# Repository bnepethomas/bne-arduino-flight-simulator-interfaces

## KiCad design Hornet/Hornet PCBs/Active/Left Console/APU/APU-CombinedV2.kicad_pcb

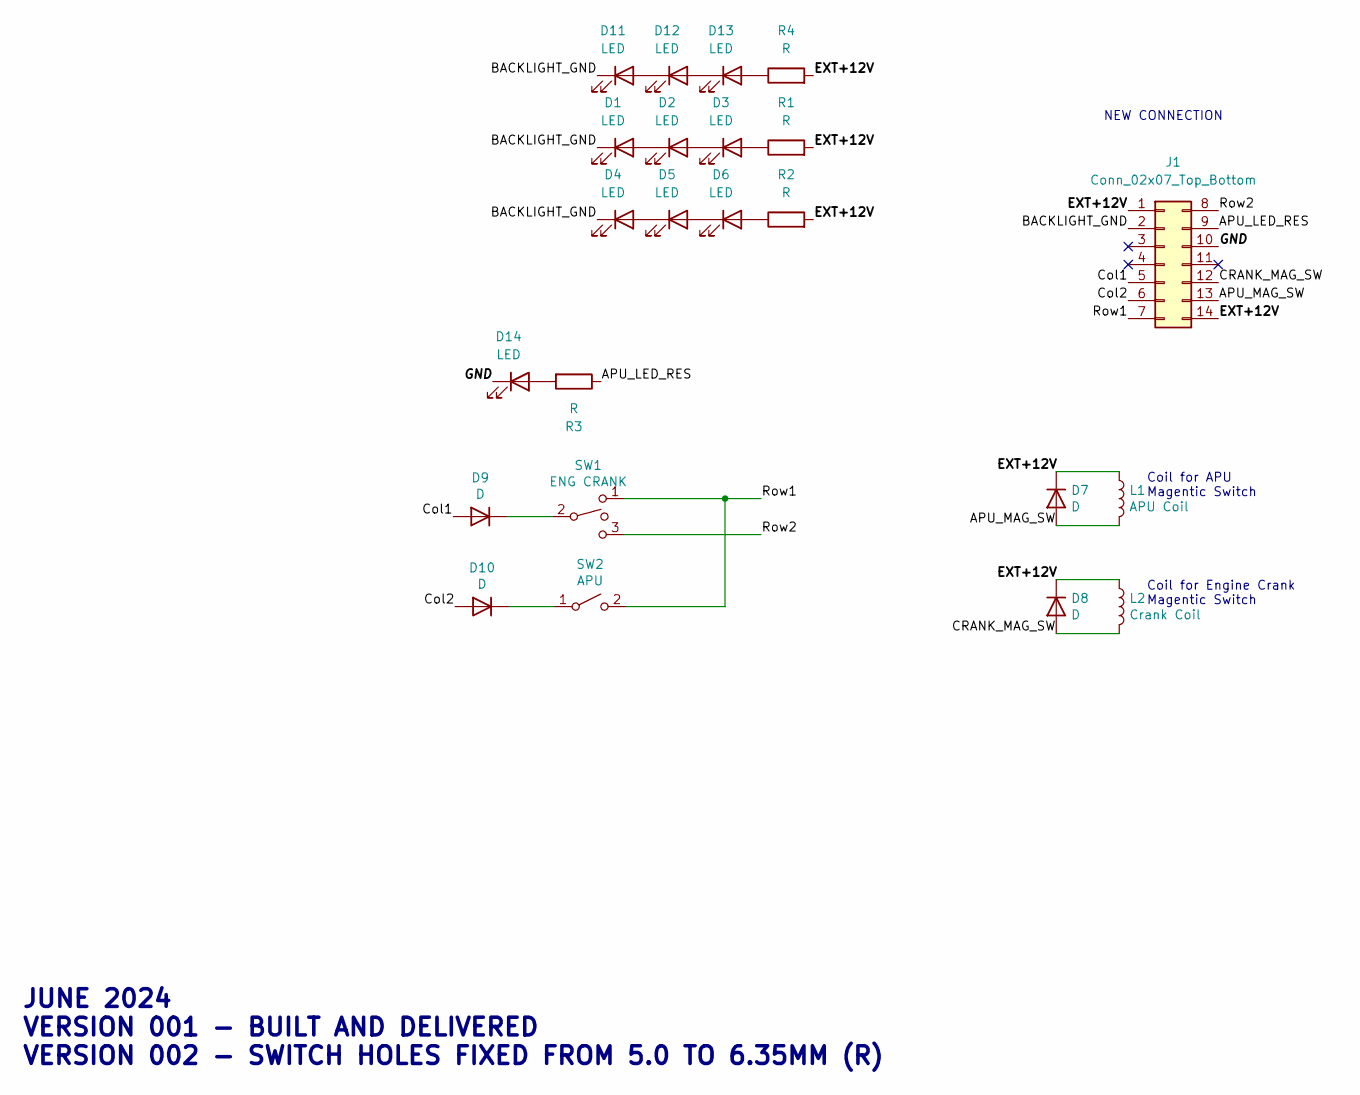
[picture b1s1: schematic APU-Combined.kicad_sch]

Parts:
D1, D2, D3, D4, D5, D6, D11, D12, D13, D14: LED; LED_D3.0mm_FlatTop
D7, D8: D; D_DO-41_SOD81_P7.62mm_Horizontal
D9, D10: D; D_A-405_P7.62mm_Horizontal-SIGNAL
J1: Conn_02x07_Top_Bottom; IDC-Header_2x07_P2.54mm_Vertical
L1: APU Coil; JST_XH_B2B-XH-A_1x02_P2.50mm_Vertical
L2: Crank Coil; JST_XH_B2B-XH-A_1x02_P2.50mm_Vertical
R1, R2, R3, R4: R; R_Axial_DIN0204_L3.6mm_D1.6mm_P7.62mm_Horizontal
SW1: ENG CRANK; JST_XH_B3B-XH-A_1x03_P2.50mm_Vertical
SW2: APU; JST_XH_B2B-XH-A_1x02_P2.50mm_Vertical

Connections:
/APU_LED_RES: J1.9, R3.1
/APU_MAG_SW: D7.2 (A), J1.13, L1.2
/BACKLIGHT_GND: D1.1 (K), D4.1 (K), D11.1 (K), J1.2
/CRANK_MAG_SW: D8.2 (A), J1.12, L2.2
/Col1: D9.2 (A), J1.5
/Col2: D10.2 (A), J1.6
/EXT+12V: D7.1 (K), D8.1 (K), J1.1, J1.14, L1.1, L2.1, R1.2, R2.2, R4.2
/GND: D14.1 (K), J1.10
/Row1: J1.7, SW1.1, SW2.2 (B)
/Row2: J1.8, SW1.3
unnamed: D1.2 (A), D2.1 (K)
unnamed: D2.2 (A), D3.1 (K)
unnamed: D3.2 (A), R1.1
unnamed: D4.2 (A), D5.1 (K)
unnamed: D5.2 (A), D6.1 (K)
unnamed: D6.2 (A), R2.1
unnamed: D9.1 (K), SW1.2
unnamed: D10.1 (K), SW2.1 (A)
unnamed: D11.2 (A), D12.1 (K)
unnamed: D12.2 (A), D13.1 (K)
unnamed: D13.2 (A), R4.1
unnamed: D14.2 (A), R3.2

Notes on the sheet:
NEW CONNECTION
Coil for Engine Crank Magentic Switch
JUNE 2024 VERSION 001 - BUILT AND DELIVERED VERSION 002 - SWITCH HOLES FIXED FROM 5.0 TO 6.35MM (R)
Coil for APU Magentic Switch

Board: 2 copper layers, 23 parts (13 on the bottom side), 22 nets, no tracks yet.

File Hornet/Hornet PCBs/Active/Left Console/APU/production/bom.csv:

Designator,Footprint,Quantity,Value,LCSC Part #
"D1, D11, D12, D13, D14, D2, D3, D4, D5, D6",LED_D3.0mm_FlatTop,10,LED,
"D10, D9",D_A-405_P7.62mm_Horizontal-SIGNAL,2,D,
"D7, D8",D_DO-41_SOD81_P7.62mm_Horizontal,2,D,
J1,IDC-Header_2x07_P2.54mm_Vertical,1,Conn_02x07_Top_Bottom,
L1,JST_XH_B2B-XH-A_1x02_P2.50mm_Vertical,1,APU Coil,
L2,JST_XH_B2B-XH-A_1x02_P2.50mm_Vertical,1,Crank Coil,
"R1, R2, R3, R4",R_Axial_DIN0204_L3.6mm_D1.6mm_P7.62mm_Horizontal,4,R,
SW1,JST_XH_B3B-XH-A_1x03_P2.50mm_Vertical,1,ENG CRANK,
SW2,JST_XH_B2B-XH-A_1x02_P2.50mm_Vertical,1,APU,

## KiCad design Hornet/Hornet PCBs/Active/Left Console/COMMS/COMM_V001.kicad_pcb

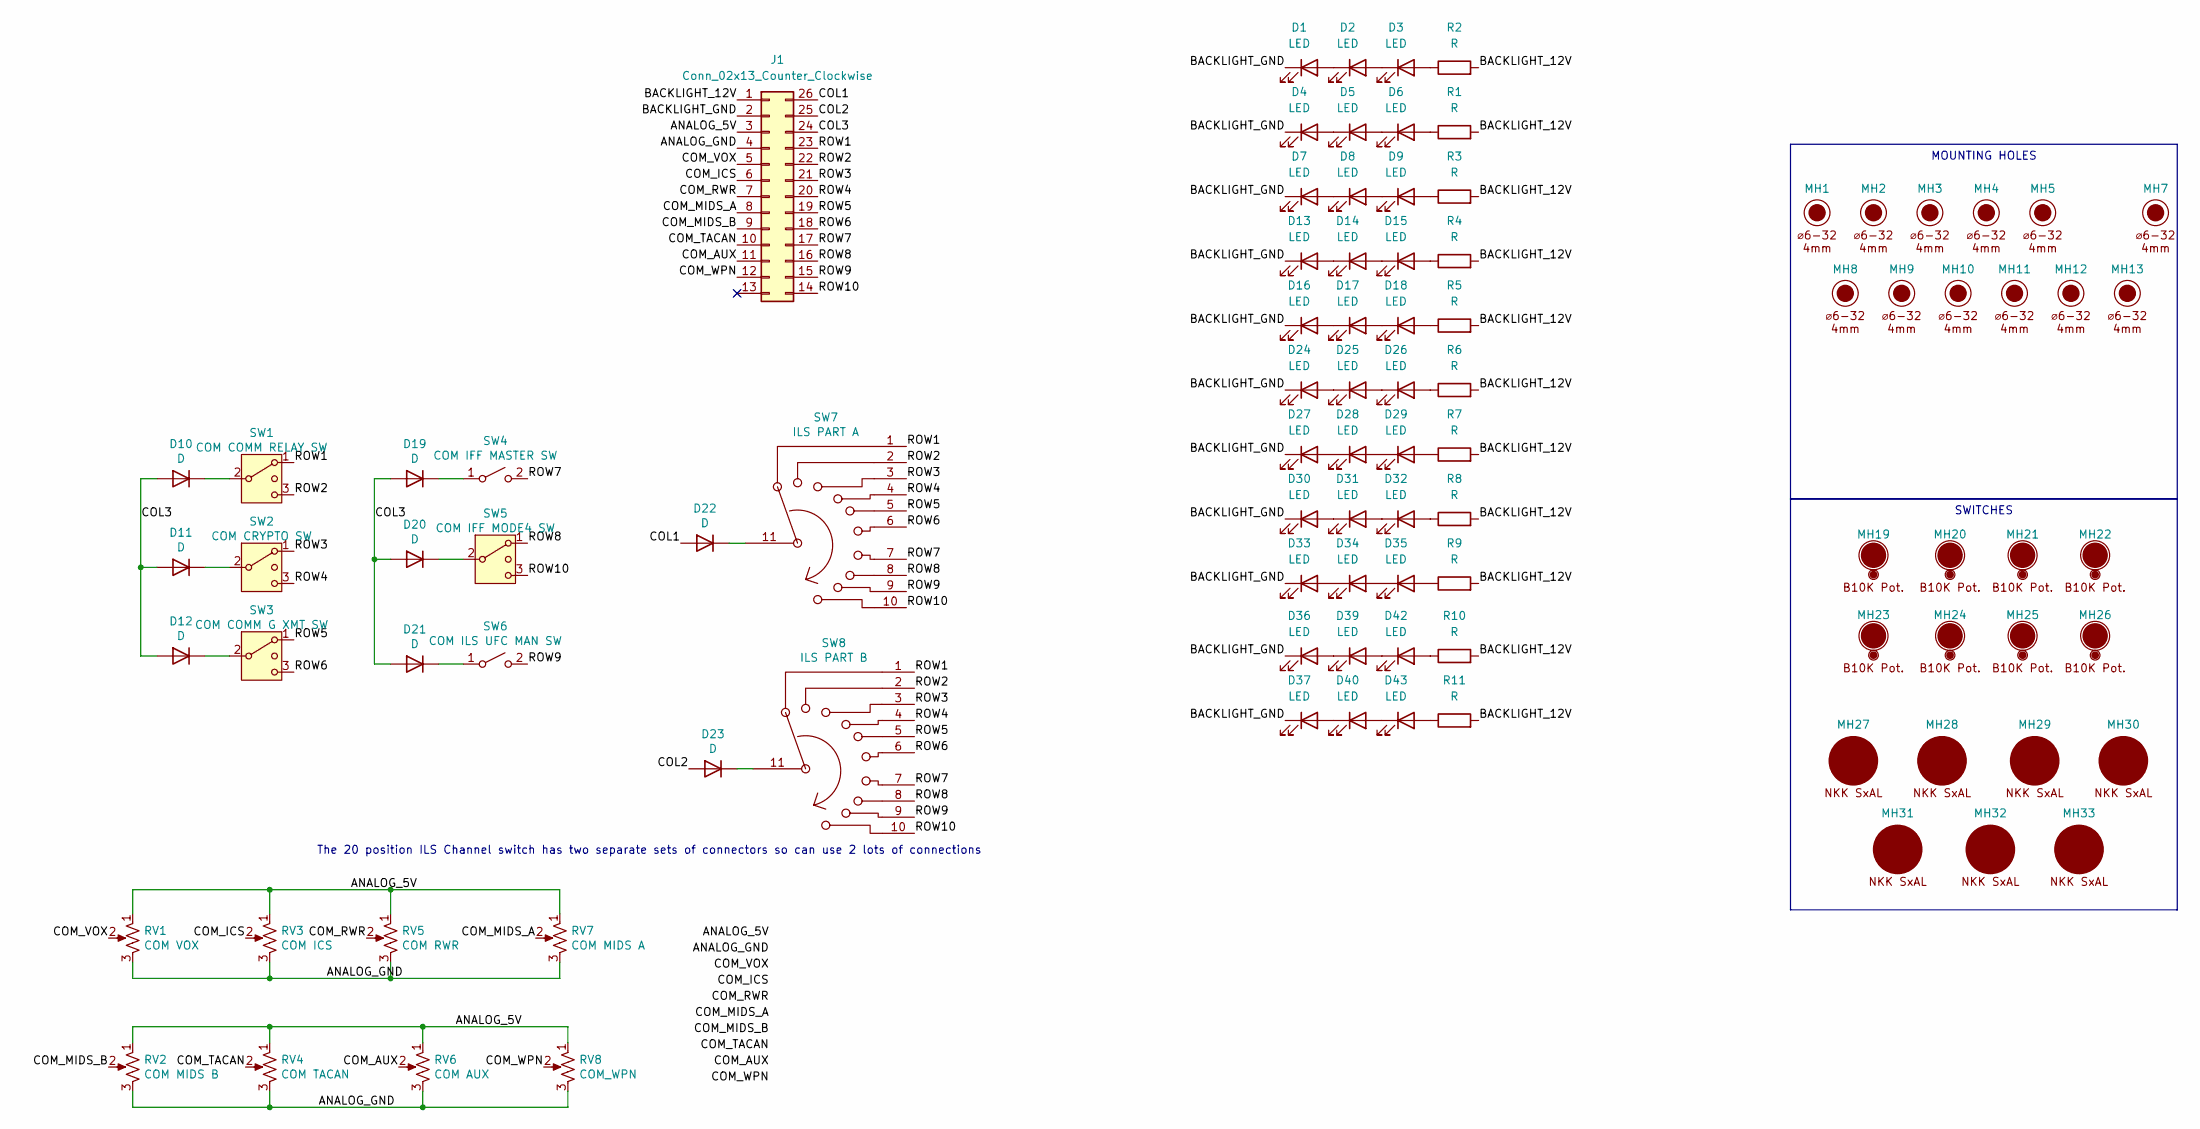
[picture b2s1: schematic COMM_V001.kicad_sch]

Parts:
D1, D2, D3, D4, D5, D6, D7, D8, D9, D13, D14, D15, D16, D17, D18, D24, D25, D26, D27, D28, D29, D30, D31, D32, D33, D34, D35, D36, D37, D39, D40, D42, D43: LED; LED_D3.0mm_FlatTop
D10, D11, D12, D19, D20, D21, D22, D23: D; D_A-405_P7.62mm_Horizontal-SIGNAL
J1: Conn_02x13_Counter_Clockwise; IDC-Header_2x13_P2.54mm_Vertical
MH1, MH2, MH3, MH4, MH5, MH7, MH8, MH9, MH10, MH11, MH12, MH13: 6x32 / 4mm; MountingHole_4.3mm_M4
MH19, MH20, MH21, MH22, MH23, MH24, MH25, MH26: Pot_B10K; BR10K_Pot_11mm_x_11mm; Manufacturer PN P0915N-FC20BR10K
MH27, MH28, MH29, MH30, MH31, MH32, MH33: Switch_NKK SxAL; SxAL_Toggle_13x13mm; Manufacturer PN SxAL
R1, R2, R3, R4, R5, R6, R7, R8, R9, R10, R11: R; R_Axial_DIN0204_L3.6mm_D1.6mm_P7.62mm_Horizontal
RV1: COM VOX; JST_XH_B3B-XH-A_1x03_P2.50mm_Vertical
RV2: COM MIDS B; JST_XH_B3B-XH-A_1x03_P2.50mm_Vertical
RV3: COM ICS; JST_XH_B3B-XH-A_1x03_P2.50mm_Vertical
RV4: COM TACAN; JST_XH_B3B-XH-A_1x03_P2.50mm_Vertical
RV5: COM RWR; JST_XH_B3B-XH-A_1x03_P2.50mm_Vertical
RV6: COM AUX; JST_XH_B3B-XH-A_1x03_P2.50mm_Vertical
RV7: COM MIDS A; JST_XH_B3B-XH-A_1x03_P2.50mm_Vertical
RV8: COM_WPN; JST_XH_B3B-XH-A_1x03_P2.50mm_Vertical
SW1: COM COMM RELAY SW; JST_XH_B3B-XH-A_1x03_P2.50mm_Vertical
SW2: COM CRYPTO SW; JST_XH_B3B-XH-A_1x03_P2.50mm_Vertical
SW3: COM COMM G XMT SW; JST_XH_B3B-XH-A_1x03_P2.50mm_Vertical
SW4: COM IFF MASTER SW; JST_XH_B2B-XH-A_1x02_P2.50mm_Vertical
SW5: COM IFF MODE4 SW; JST_XH_B3B-XH-A_1x03_P2.50mm_Vertical
SW6: COM ILS UFC MAN SW; JST_XH_B2B-XH-A_1x02_P2.50mm_Vertical
SW7: ILS PART A; JST_XH_B12B-XH-A_1x12_P2.50mm_Vertical
SW8: ILS PART B; JST_XH_B12B-XH-A_1x12_P2.50mm_Vertical

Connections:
/ANALOG_5V: J1.3, RV1.1, RV2.1, RV3.1, RV4.1, RV5.1, RV6.1, RV7.1, RV8.1
/ANALOG_GND: J1.4, RV1.3, RV2.3, RV3.3, RV4.3, RV5.3, RV6.3, RV7.3, RV8.3
/BACKLIGHT_12V: J1.1, R1.2, R2.2, R3.2, R4.2, R5.2, R6.2, R7.2, R8.2, R9.2, R10.2, R11.2
/BACKLIGHT_GND: D1.1 (K), D4.1 (K), D7.1 (K), D13.1 (K), D16.1 (K), D24.1 (K), D27.1 (K), D30.1 (K), D33.1 (K), D36.1 (K), D37.1 (K), J1.2
/COL1: D22.2 (A), J1.26
/COL2: D23.2 (A), J1.25
/COL3: D10.2 (A), D11.2 (A), D12.2 (A), D19.2 (A), D20.2 (A), D21.2 (A), J1.24
/COM_AUX: J1.11, RV6.2
/COM_ICS: J1.6, RV3.2
/COM_MIDS_A: J1.8, RV7.2
/COM_MIDS_B: J1.9, RV2.2
/COM_RWR: J1.7, RV5.2
/COM_TACAN: J1.10, RV4.2
/COM_VOX: J1.5, RV1.2
/COM_WPN: J1.12, RV8.2
/ROW1: J1.23, SW1.1, SW7.1, SW8.1
/ROW2: J1.22, SW1.3 (4), SW7.2, SW8.2
/ROW3: J1.21, SW2.1, SW7.3, SW8.3
/ROW4: J1.20, SW2.3 (4), SW7.4, SW8.4
/ROW5: J1.19, SW3.1, SW7.5, SW8.5
/ROW6: J1.18, SW3.3 (4), SW7.6, SW8.6
/ROW7: J1.17, SW4.2 (B), SW7.7, SW8.7
/ROW8: J1.16, SW5.1, SW7.8, SW8.8
/ROW9: J1.15, SW6.2 (B), SW7.9, SW8.9
/ROW10: J1.14, SW5.3 (4), SW7.10, SW8.10
unnamed: D1.2 (A), D2.1 (K)
unnamed: D2.2 (A), D3.1 (K)
unnamed: D3.2 (A), R2.1
unnamed: D4.2 (A), D5.1 (K)
unnamed: D5.2 (A), D6.1 (K)
unnamed: D6.2 (A), R1.1
unnamed: D7.2 (A), D8.1 (K)
unnamed: D8.2 (A), D9.1 (K)
unnamed: D9.2 (A), R3.1
unnamed: D10.1 (K), SW1.2 (3)
unnamed: D11.1 (K), SW2.2 (3)
unnamed: D12.1 (K), SW3.2 (3)
unnamed: D13.2 (A), D14.1 (K)
unnamed: D14.2 (A), D15.1 (K)
unnamed: D15.2 (A), R4.1
unnamed: D16.2 (A), D17.1 (K)
unnamed: D17.2 (A), D18.1 (K)
unnamed: D18.2 (A), R5.1
unnamed: D19.1 (K), SW4.1 (A)
unnamed: D20.1 (K), SW5.2 (3)
unnamed: D21.1 (K), SW6.1 (A)
unnamed: D22.1 (K), SW7.11
unnamed: D23.1 (K), SW8.11
unnamed: D24.2 (A), D25.1 (K)
unnamed: D25.2 (A), D26.1 (K)
unnamed: D26.2 (A), R6.1
unnamed: D27.2 (A), D28.1 (K)
unnamed: D28.2 (A), D29.1 (K)
unnamed: D29.2 (A), R7.1
unnamed: D30.2 (A), D31.1 (K)
unnamed: D31.2 (A), D32.1 (K)
unnamed: D32.2 (A), R8.1
unnamed: D33.2 (A), D34.1 (K)
unnamed: D34.2 (A), D35.1 (K)
unnamed: D35.2 (A), R9.1
unnamed: D36.2 (A), D39.1 (K)
unnamed: D37.2 (A), D40.1 (K)
unnamed: D39.2 (A), D42.1 (K)
unnamed: D40.2 (A), D43.1 (K)
unnamed: D42.2 (A), R10.1
unnamed: D43.2 (A), R11.1

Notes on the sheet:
MOUNTING HOLES
SWITCHES
The 20 position ILS Channel switch has two separate sets of connectors so can use 2 lots of connections

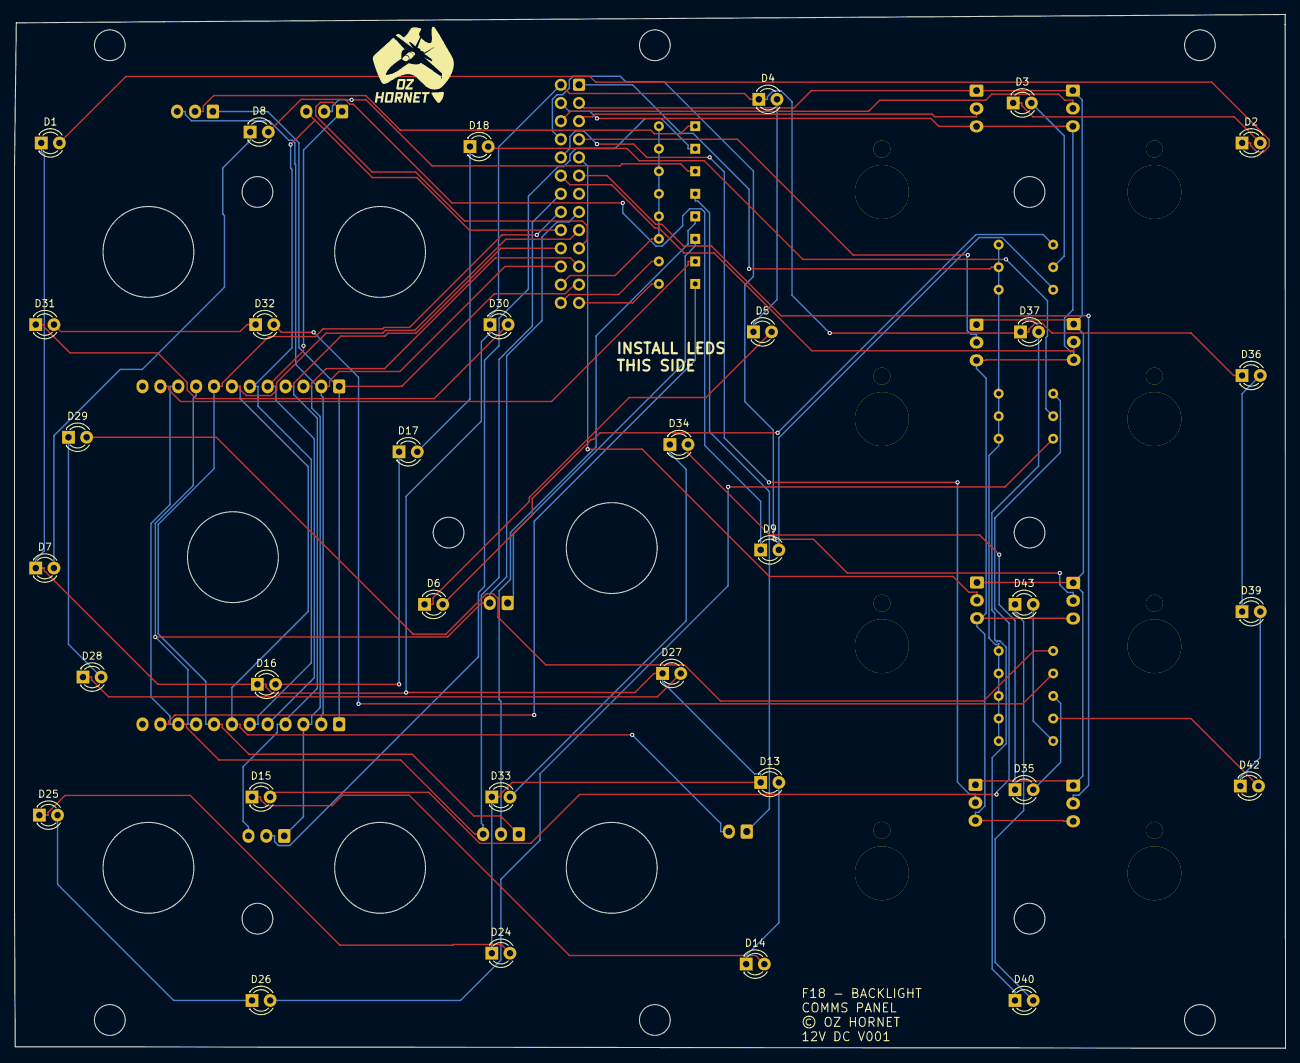
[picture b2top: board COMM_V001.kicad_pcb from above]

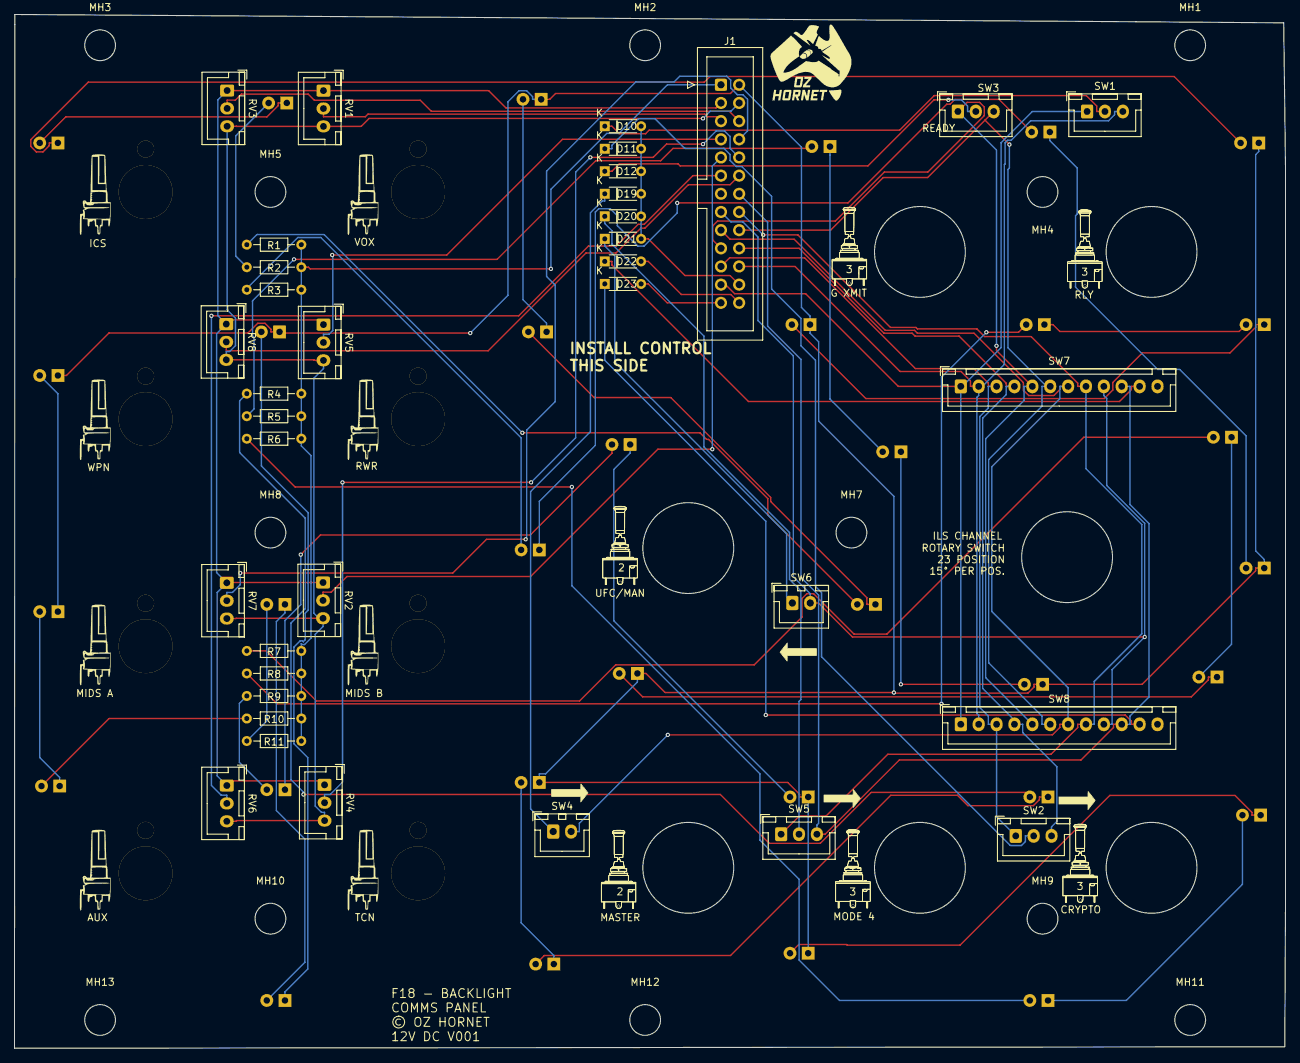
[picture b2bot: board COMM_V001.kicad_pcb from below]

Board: 2 copper layers, 177.7 x 144.5 mm, 110 parts (62 on the bottom side), 66 nets.

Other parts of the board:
LOGO3, LOGO4, LOGO12, LOGO13: LOGO; S3AL_Toggle_Silkscreen
LOGO5, LOGO6, LOGO7, LOGO8, LOGO10, LOGO11, LOGO15, LOGO16: LOGO; BR10KPot
LOGO9, LOGO14: LOGO; S2AL_Toggle_Silkscreen

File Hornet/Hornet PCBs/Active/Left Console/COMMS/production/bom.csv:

Designator,Footprint,Quantity,Value,LCSC Part #
"D1, D13, D14, D15, D16, D17, D18, D2, D24, D25, D26, D27, D28, D29, D3, D30, D31, D32, D33, D34, D35, D36, D37, D39, D4, D40, D42, D43, D5, D6, D7, D8, D9",LED_D3.0mm_FlatTop,33,LED,
"D10, D11, D12, D19, D20, D21, D22, D23",D_A-405_P7.62mm_Horizontal-SIGNAL,8,D,
J1,IDC-Header_2x13_P2.54mm_Vertical,1,Conn_02x13_Counter_Clockwise,
"R1, R10, R11, R2, R3, R4, R5, R6, R7, R8, R9",R_Axial_DIN0204_L3.6mm_D1.6mm_P7.62mm_Horizontal,11,R,
RV1,JST_XH_B3B-XH-A_1x03_P2.50mm_Vertical,1,COM VOX,
RV2,JST_XH_B3B-XH-A_1x03_P2.50mm_Vertical,1,COM MIDS B,
RV3,JST_XH_B3B-XH-A_1x03_P2.50mm_Vertical,1,COM ICS,
RV4,JST_XH_B3B-XH-A_1x03_P2.50mm_Vertical,1,COM TACAN,
RV5,JST_XH_B3B-XH-A_1x03_P2.50mm_Vertical,1,COM RWR,
RV6,JST_XH_B3B-XH-A_1x03_P2.50mm_Vertical,1,COM AUX,
RV7,JST_XH_B3B-XH-A_1x03_P2.50mm_Vertical,1,COM MIDS A,
RV8,JST_XH_B3B-XH-A_1x03_P2.50mm_Vertical,1,COM_WPN,
SW1,JST_XH_B3B-XH-A_1x03_P2.50mm_Vertical,1,COM COMM RELAY SW,
SW2,JST_XH_B3B-XH-A_1x03_P2.50mm_Vertical,1,COM CRYPTO SW,
SW3,JST_XH_B3B-XH-A_1x03_P2.50mm_Vertical,1,COM COMM G XMT SW,
SW4,JST_XH_B2B-XH-A_1x02_P2.50mm_Vertical,1,COM IFF MASTER SW,
SW5,JST_XH_B3B-XH-A_1x03_P2.50mm_Vertical,1,COM IFF MODE4 SW,
SW6,JST_XH_B2B-XH-A_1x02_P2.50mm_Vertical,1,COM ILS UFC MAN SW,
SW7,JST_XH_B12B-XH-A_1x12_P2.50mm_Vertical,1,ILS PART A,
SW8,JST_XH_B12B-XH-A_1x12_P2.50mm_Vertical,1,ILS PART B,

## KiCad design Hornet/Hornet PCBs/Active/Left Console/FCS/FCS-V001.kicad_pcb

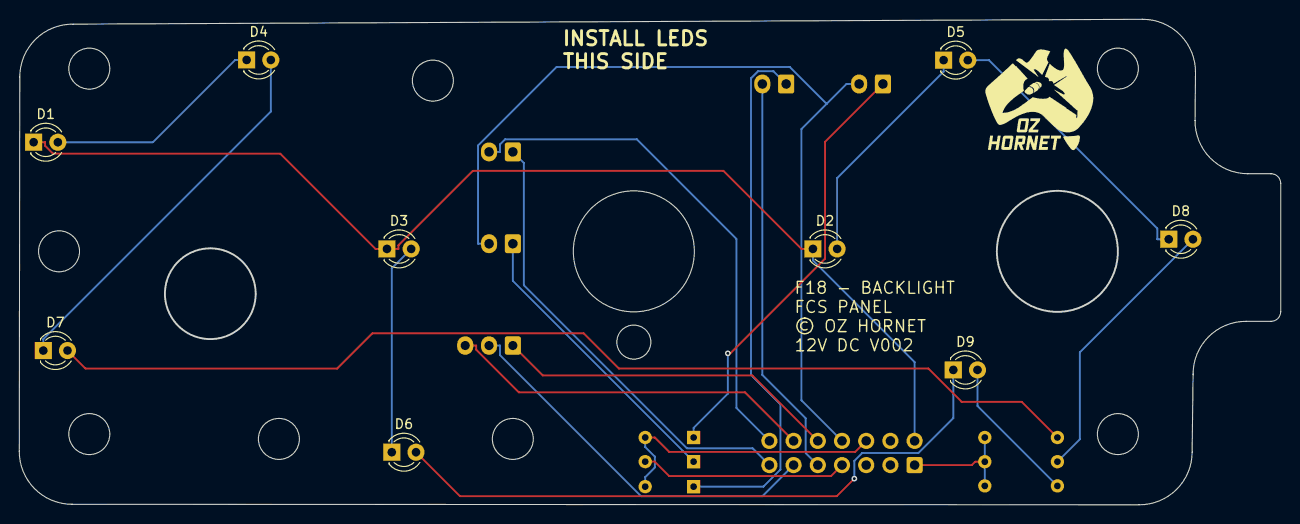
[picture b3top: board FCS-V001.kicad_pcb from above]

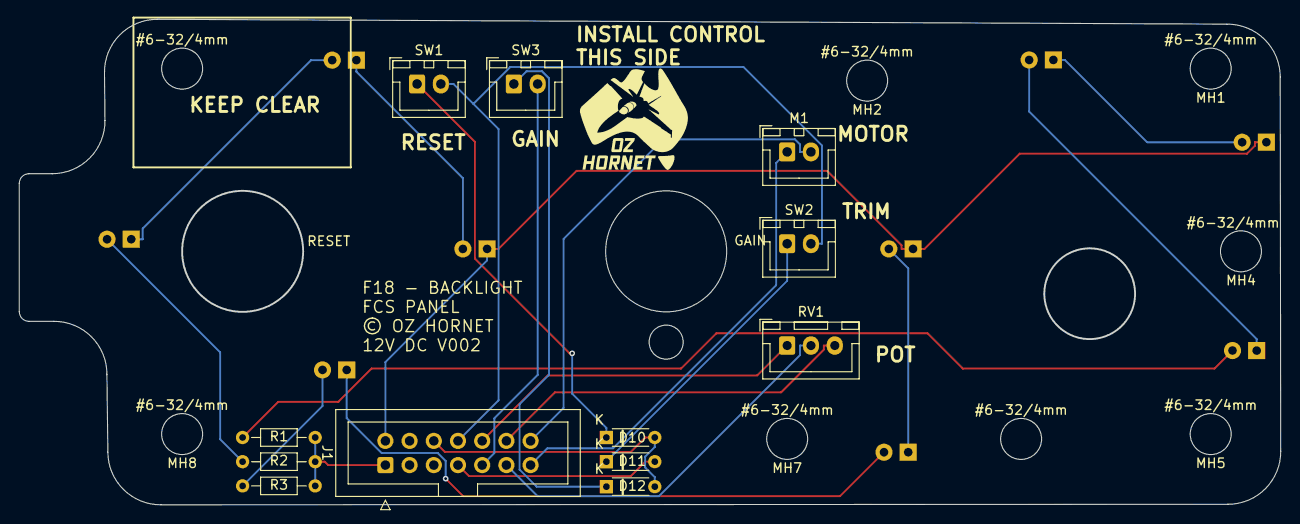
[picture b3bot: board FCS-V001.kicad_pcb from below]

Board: 2 copper layers, 132.4 x 51.0 mm, 30 parts (20 on the bottom side), 23 nets.

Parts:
D1, D2, D3, D4, D5, D6, D7, D8, D9: LED; LED_D3.0mm_FlatTop
D10, D11, D12: D; D_A-405_P7.62mm_Horizontal-SIGNAL
J1: Conn_02x07_Top_Bottom; IDC-Header_2x07_P2.54mm_Vertical
M1: Motor_DC; JST_XH_B2B-XH-A_1x02_P2.50mm_Vertical
MH1, MH2, MH3, MH4, MH5, MH6, MH7, MH8: 6x32 / 4mm; MountingHole_6-32_PHS
MH9: Switch_100SPx; 100SPX_Toggle_13mm_x_18mm
R1, R2, R3: R; R_Axial_DIN0204_L3.6mm_D1.6mm_P7.62mm_Horizontal
RV1: RUD TRIM; JST_XH_B3B-XH-A_1x03_P2.50mm_Vertical
SW1: FCS RESET BTN; JST_XH_B2B-XH-A_1x02_P2.50mm_Vertical
SW2: TO TRIM BTN; JST_XH_B2B-XH-A_1x02_P2.50mm_Vertical
SW3: GAIN SWITCH; JST_XH_B2B-XH-A_1x02_P2.50mm_Vertical

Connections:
/BACKLIGHT_GND: D1.1 (K), D2.1 (K), D3.1 (K), J1.2
/Col1: D10.2 (A), D12.2 (A), J1.6
/Col2: D11.2 (A), J1.7
/EXT+12V: J1.1, R1.2, R2.2, R3.2
/GND: J1.12, RV1.3
/INT_5V+: J1.10, RV1.1
/RUD_TRIM: J1.11, RV1.2
/RUD_TRIM_M+: J1.13, M1.1 (+)
/RUD_TRIM_M-: J1.14, M1.2 (-)
/Row1: J1.8, SW1.2, SW2.2
/Row2: J1.9, SW3.2 (B)
unnamed: D1.2 (A), D4.1 (K)
unnamed: D2.2 (A), D5.1 (K)
unnamed: D3.2 (A), D6.1 (K)
unnamed: D4.2 (A), D7.1 (K)
unnamed: D5.2 (A), D8.1 (K)
unnamed: D6.2 (A), D9.1 (K)
unnamed: D7.2 (A), R1.1
unnamed: D8.2 (A), R2.1
unnamed: D9.2 (A), R3.1
unnamed: D10.1 (K), SW1.1
unnamed: D11.1 (K), SW2.1
unnamed: D12.1 (K), SW3.1 (A)

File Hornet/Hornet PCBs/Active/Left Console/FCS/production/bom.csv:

Designator,Footprint,Quantity,Value,LCSC Part #
"D1, D2, D3, D4, D5, D6, D7, D8, D9",LED_D3.0mm_FlatTop,9,LED,
"D10, D11, D12",D_A-405_P7.62mm_Horizontal-SIGNAL,3,D,
J1,IDC-Header_2x07_P2.54mm_Vertical,1,Conn_02x07_Top_Bottom,
M1,JST_XH_B2B-XH-A_1x02_P2.50mm_Vertical,1,Motor_DC,
"R1, R2, R3",R_Axial_DIN0204_L3.6mm_D1.6mm_P7.62mm_Horizontal,3,R,
RV1,JST_XH_B3B-XH-A_1x03_P2.50mm_Vertical,1,RUD TRIM,
SW1,JST_XH_B2B-XH-A_1x02_P2.50mm_Vertical,1,FCS RESET BTN,
SW2,JST_XH_B2B-XH-A_1x02_P2.50mm_Vertical,1,TO TRIM BTN,
SW3,JST_XH_B2B-XH-A_1x02_P2.50mm_Vertical,1,GAIN SWITCH,

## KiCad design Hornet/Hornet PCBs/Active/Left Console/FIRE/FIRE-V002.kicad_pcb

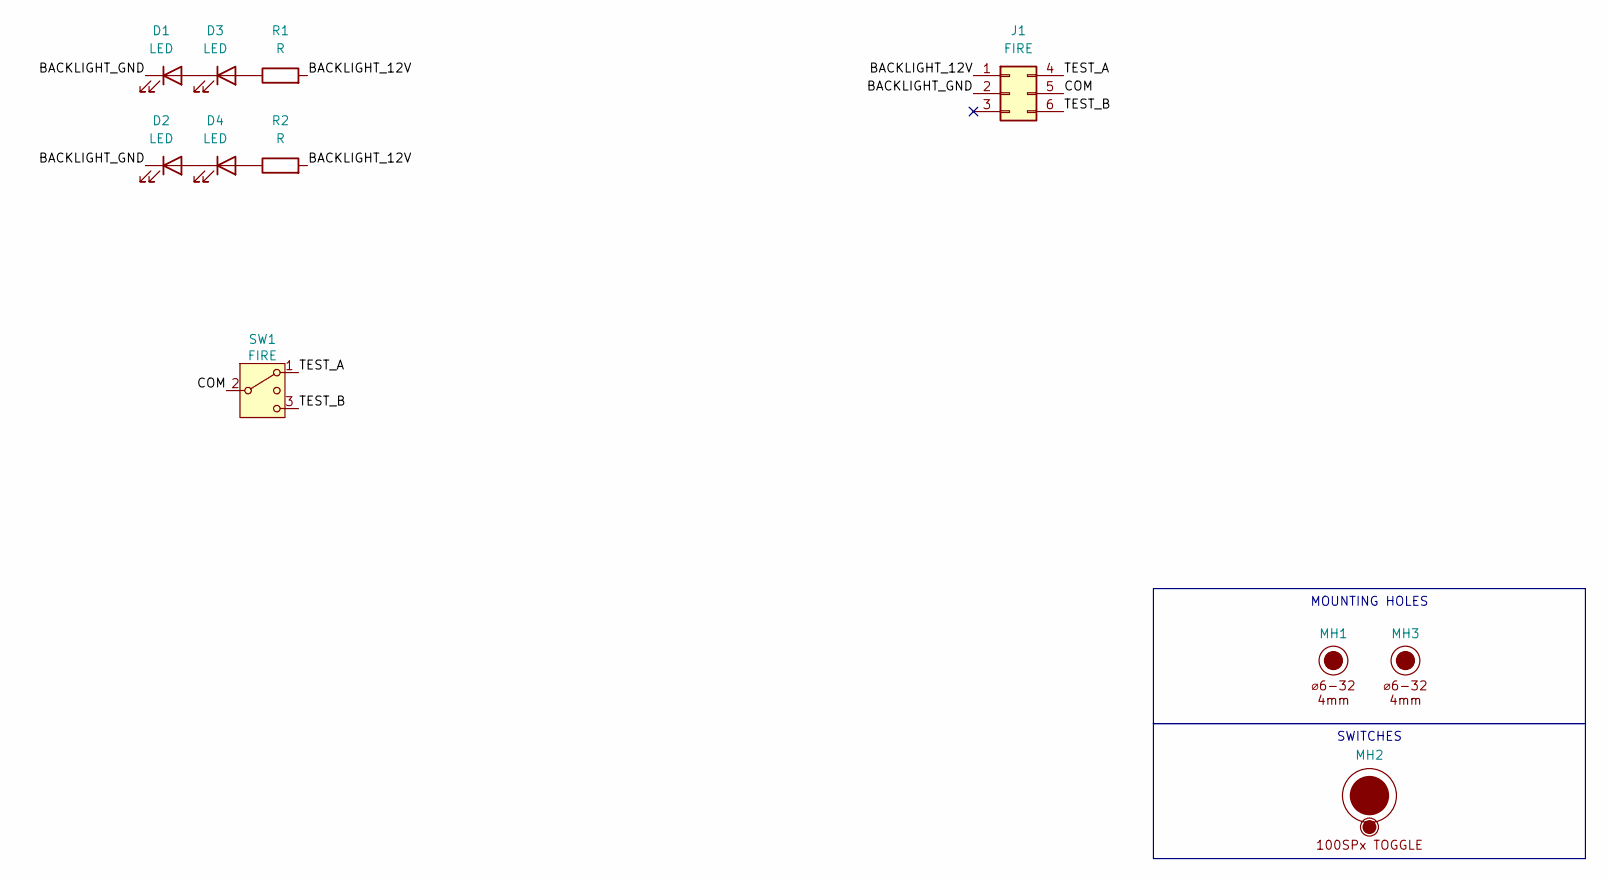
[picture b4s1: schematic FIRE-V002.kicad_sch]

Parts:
D1, D2, D3, D4: LED; LED_D3.0mm_FlatTop
J1: FIRE; IDC-Header_2x03_P2.54mm_Vertical
MH1, MH3: 6x32 / 4mm; MountingHole_6-32_PHS
MH2: Switch_100SPx; 100SPX_Toggle_13mm_x_18mm
R1, R2: R; R_Axial_DIN0204_L3.6mm_D1.6mm_P7.62mm_Horizontal
SW1: FIRE; Molex_KK-254_AE-6410-03A_1x03_P2.54mm_Vertical

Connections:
/BACKLIGHT_12V: J1.1, R1.2, R2.2
/BACKLIGHT_GND: D1.1 (K), D2.1 (K), J1.2
/COM: J1.5, SW1.2 (3)
/TEST_A: J1.4, SW1.1
/TEST_B: J1.6, SW1.3 (4)
unnamed: D1.2 (A), D3.1 (K)
unnamed: D2.2 (A), D4.1 (K)
unnamed: D3.2 (A), R1.1
unnamed: D4.2 (A), R2.1

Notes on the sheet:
SWITCHES
MOUNTING HOLES

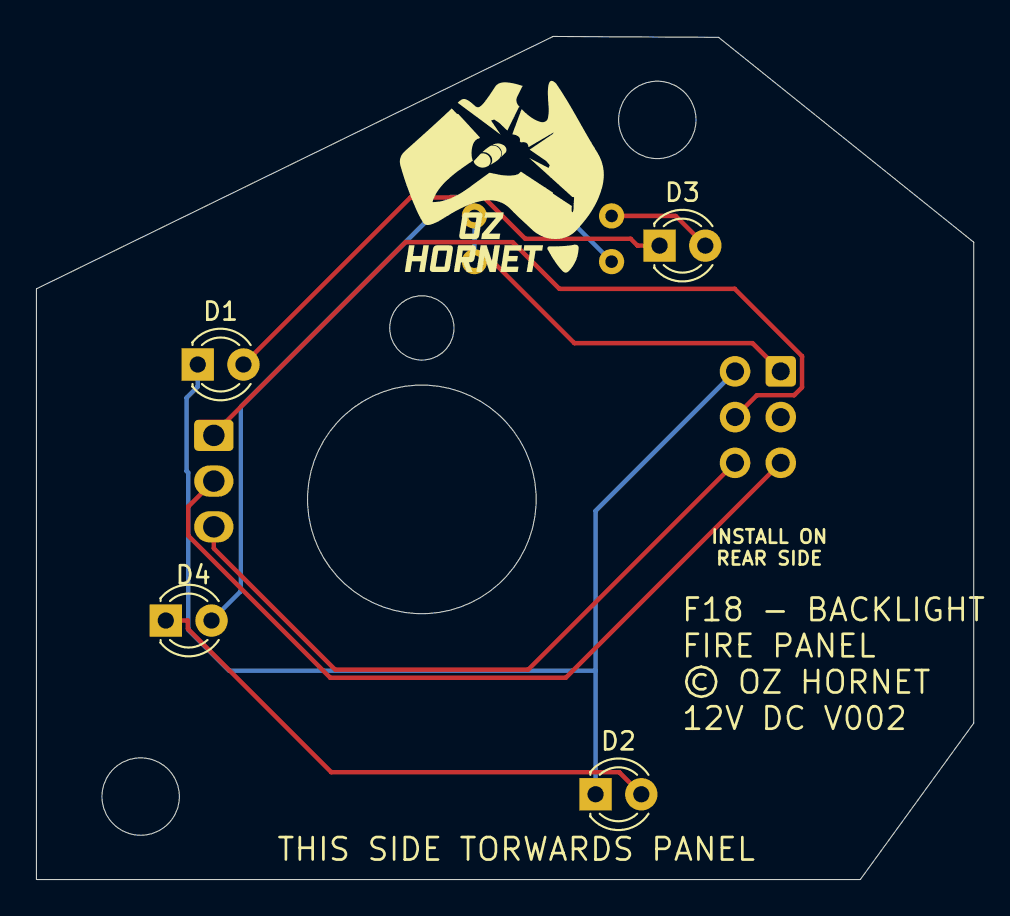
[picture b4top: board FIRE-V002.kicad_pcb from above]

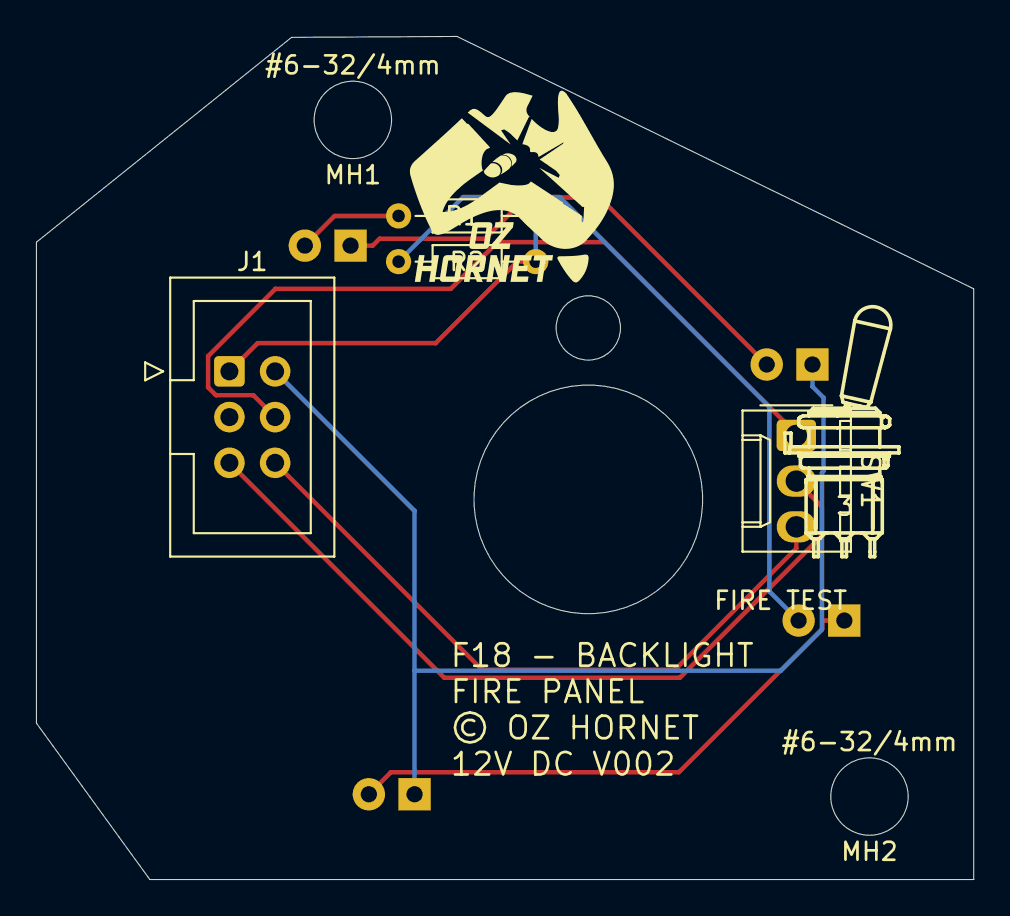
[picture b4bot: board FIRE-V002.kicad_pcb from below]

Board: 2 copper layers, 52.1 x 46.8 mm, 12 parts (7 on the bottom side), 9 nets.

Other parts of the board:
LOGO3: LOGO; 100SP3_Toggle_Silkscreen

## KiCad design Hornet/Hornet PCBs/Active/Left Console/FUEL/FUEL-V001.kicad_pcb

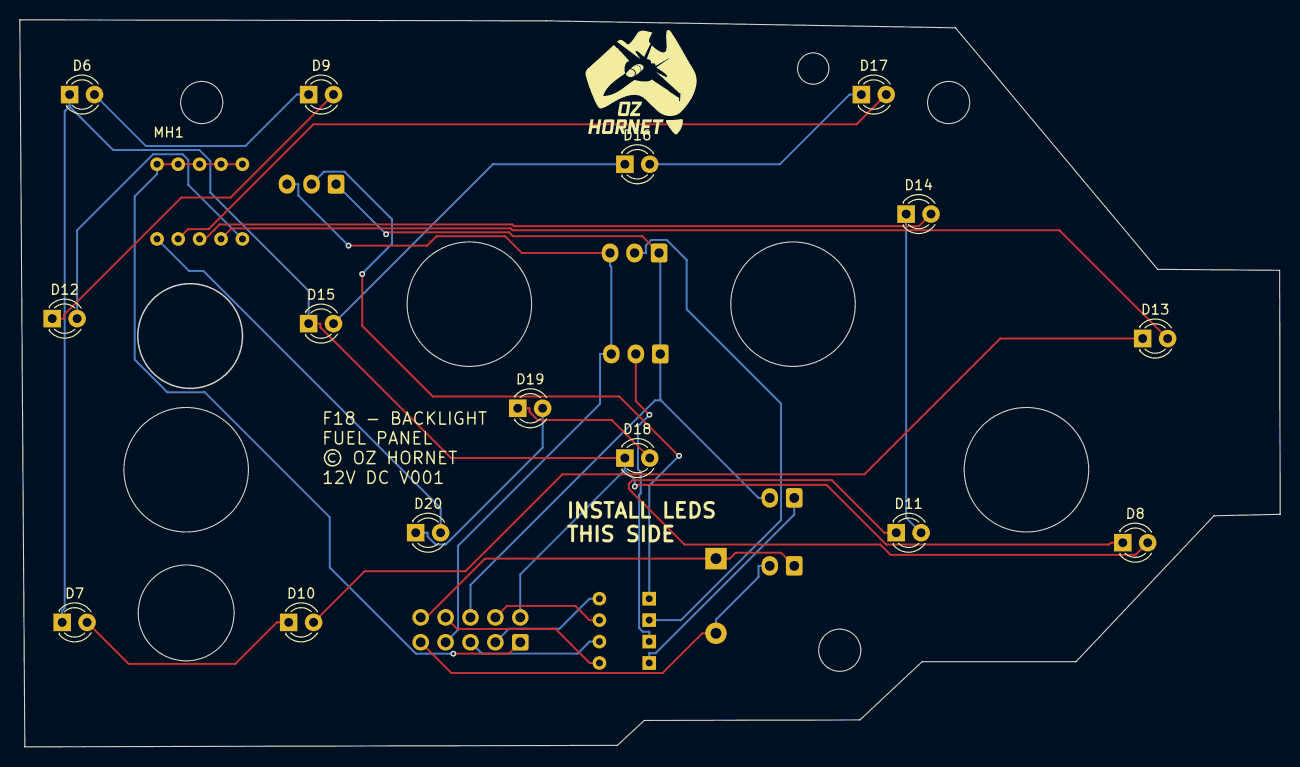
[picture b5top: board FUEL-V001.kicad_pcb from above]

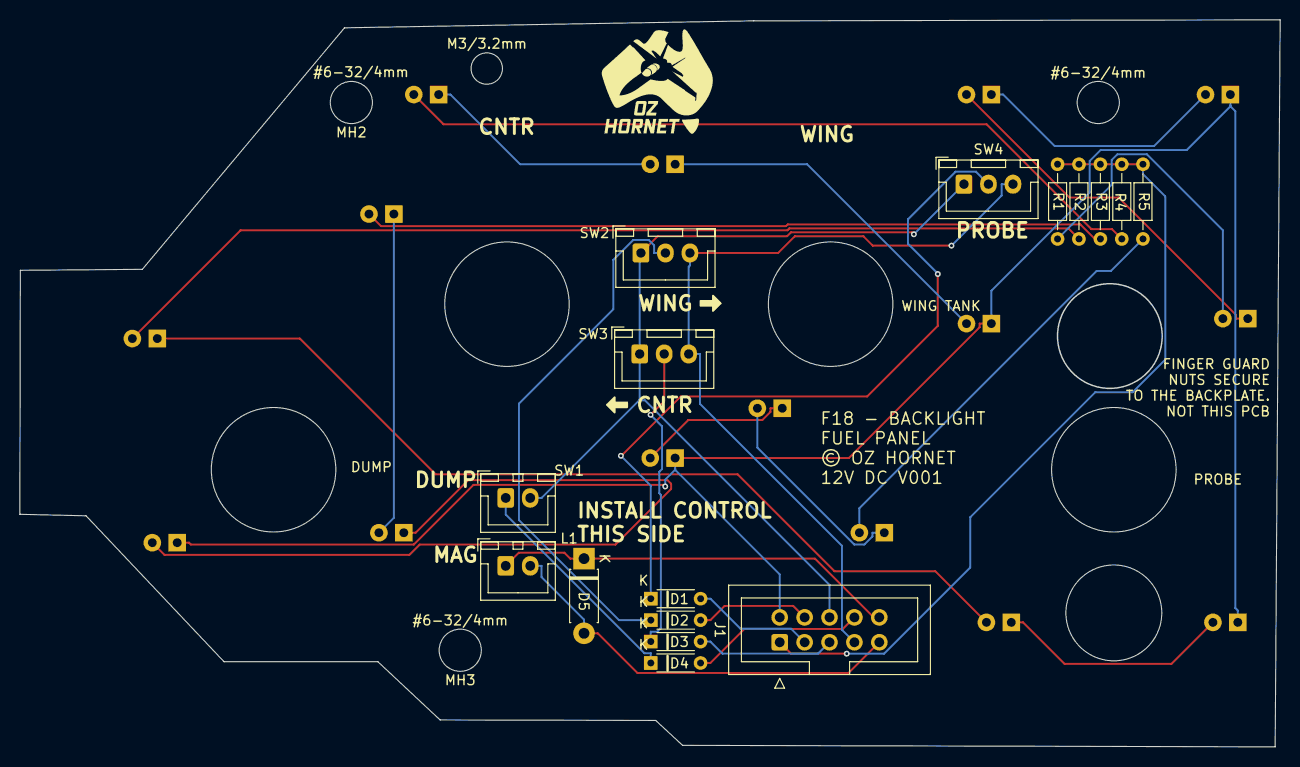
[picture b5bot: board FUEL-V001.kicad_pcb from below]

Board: 2 copper layers, 128.6 x 74.2 mm, 39 parts (20 on the bottom side), 29 nets.

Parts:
D1, D2, D3, D4: D; D_A-405_P7.62mm_Horizontal-SIGNAL
D5: D; D_DO-41_SOD81_P7.62mm_Horizontal
D6, D7, D8, D9, D10, D11, D12, D13, D14, D15, D16, D17, D18, D19, D20: LED; LED_D3.0mm_FlatTop
J1: Conn_02x05_Top_Bottom; IDC-Header_2x05_P2.54mm_Vertical
L1: APU Coil; JST_XH_B2B-XH-A_1x02_P2.50mm_Vertical
MH1, MH2, MH3: 6x32 / 4mm; MountingHole_6-32_PHS
MH6: M3 / 3.2mm; MountingHole_3.2mm_M3_DIN965
MH9, MH12: Switch_631H; 631HX_Toggle_13mm_x_13mm
MH10, MH11: Switch_NKK SxAL; SxAL_Toggle_13x13mm
R1, R2, R3, R4, R5: R; R_Axial_DIN0204_L3.6mm_D1.6mm_P7.62mm_Horizontal
SW1: Dump; JST_XH_B2B-XH-A_1x02_P2.50mm_Vertical
SW2: Wing; JST_XH_B3B-XH-A_1x03_P2.50mm_Vertical
SW3: CTR; JST_XH_B3B-XH-A_1x03_P2.50mm_Vertical
SW4: Probe; JST_XH_B3B-XH-A_1x03_P2.50mm_Vertical

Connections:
/BACKLIGHT_12V: J1.1, R1.2, R2.2, R3.2, R4.2, R5.2
/BACKLIGHT_GND: D6.1 (K), D7.1 (K), D8.1 (K), D15.1 (K), D18.1 (K), J1.2
/Col0: D1.2 (A), J1.3
/Col1: D2.2 (A), J1.4
/Col2: D3.2 (A), J1.5
/Col3: D4.2 (A), J1.8
/FUEL_MAG_SW: D5.2 (A), J1.9, L1.2
/MAG_VOLTS_5_OR_12: D5.1 (K), J1.10, L1.1
/Row1: J1.6, SW1.2 (B), SW2.1, SW3.1, SW4.1
/Row2: J1.7, SW2.3 (4), SW3.3 (4), SW4.3 (4)
unnamed: D1.1 (K), SW4.2 (3)
unnamed: D2.1 (K), SW2.2 (3)
unnamed: D3.1 (K), SW3.2 (3)
unnamed: D4.1 (K), SW1.1 (A)
unnamed: D6.2 (A), D9.1 (K)
unnamed: D10.2 (A), D13.1 (K)
unnamed: D7.2 (A), D10.1 (K)
unnamed: D11.2 (A), D14.1 (K)
unnamed: D8.2 (A), D11.1 (K)
unnamed: D12.2 (A), R1.1
unnamed: D9.2 (A), D12.1 (K)
unnamed: D13.2 (A), R2.1
unnamed: D14.2 (A), R3.1
unnamed: D15.2 (A), D16.1 (K)
unnamed: D16.2 (A), D17.1 (K)
unnamed: D17.2 (A), R4.1
unnamed: D18.2 (A), D19.1 (K)
unnamed: D19.2 (A), D20.1 (K)
unnamed: D20.2 (A), R5.1

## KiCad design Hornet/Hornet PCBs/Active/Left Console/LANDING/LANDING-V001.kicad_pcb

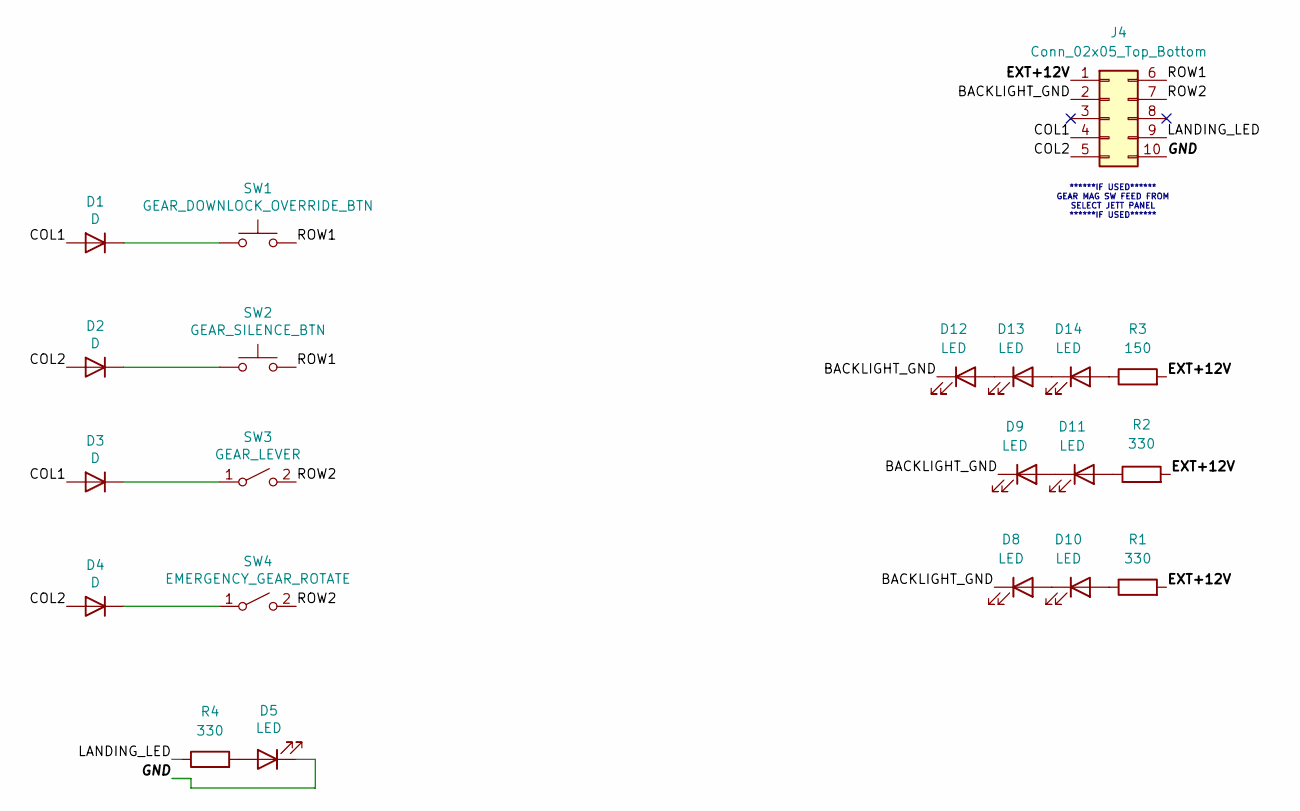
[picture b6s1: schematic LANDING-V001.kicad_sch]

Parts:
D1, D2, D3, D4: D; D_A-405_P7.62mm_Horizontal-SIGNAL
D5: LED; JST_XH_B2B-XH-A_1x02_P2.50mm_Vertical
D8, D9, D10, D11, D12, D13, D14: LED; LED_D3.0mm_FlatTop
J4: Conn_02x05_Top_Bottom; IDC-Header_2x05_P2.54mm_Vertical
R1, R2, R4: 330; R_Axial_DIN0204_L3.6mm_D1.6mm_P7.62mm_Horizontal
R3: 150; R_Axial_DIN0204_L3.6mm_D1.6mm_P7.62mm_Horizontal
SW1: GEAR_DOWNLOCK_OVERRIDE_BTN; JST_XH_B2B-XH-A_1x02_P2.50mm_Vertical
SW2: GEAR_SILENCE_BTN; JST_XH_B2B-XH-A_1x02_P2.50mm_Vertical
SW3: GEAR_LEVER; JST_XH_B2B-XH-A_1x02_P2.50mm_Vertical
SW4: EMERGENCY_GEAR_ROTATE; JST_XH_B2B-XH-A_1x02_P2.50mm_Vertical

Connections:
/BACKLIGHT_GND: D8.1 (K), D9.1 (K), D12.1 (K), J4.2
/COL1: D1.2 (A), D3.2 (A), J4.4
/COL2: D2.2 (A), D4.2 (A), J4.5
/EXT+12V: J4.1, R1.2, R2.2, R3.2
/GND: D5.1 (K), J4.10
/LANDING_LED: J4.9, R4.1
/ROW1: J4.6, SW1.2, SW2.2
/ROW2: J4.7, SW3.2 (B), SW4.2 (B)
unnamed: D1.1 (K), SW1.1
unnamed: D2.1 (K), SW2.1
unnamed: D3.1 (K), SW3.1 (A)
unnamed: D4.1 (K), SW4.1 (A)
unnamed: D5.2 (A), R4.2
unnamed: D10.2 (A), R1.1
unnamed: D8.2 (A), D10.1 (K)
unnamed: D11.2 (A), R2.1
unnamed: D9.2 (A), D11.1 (K)
unnamed: D12.2 (A), D13.1 (K)
unnamed: D13.2 (A), D14.1 (K)
unnamed: D14.2 (A), R3.1

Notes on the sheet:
******IF USED****** GEAR MAG SW FEED FROM SELECT JETT PANEL ******IF USED******

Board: 2 copper layers, 29 parts (22 on the bottom side), 20 nets, no tracks yet.

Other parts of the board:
MH1, MH2, MH3, MH4, MH5, MH6, MH7, MH8: 6x32 / 4mm; MountingHole_6-32_PHS

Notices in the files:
Hornet/Hornet PCBs/Active/Left Console/APU/APU-CombinedV2.kicad_pcb:
© OZ HORNET
